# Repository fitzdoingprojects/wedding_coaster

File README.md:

# wedding_coaster
Wedding Coaster

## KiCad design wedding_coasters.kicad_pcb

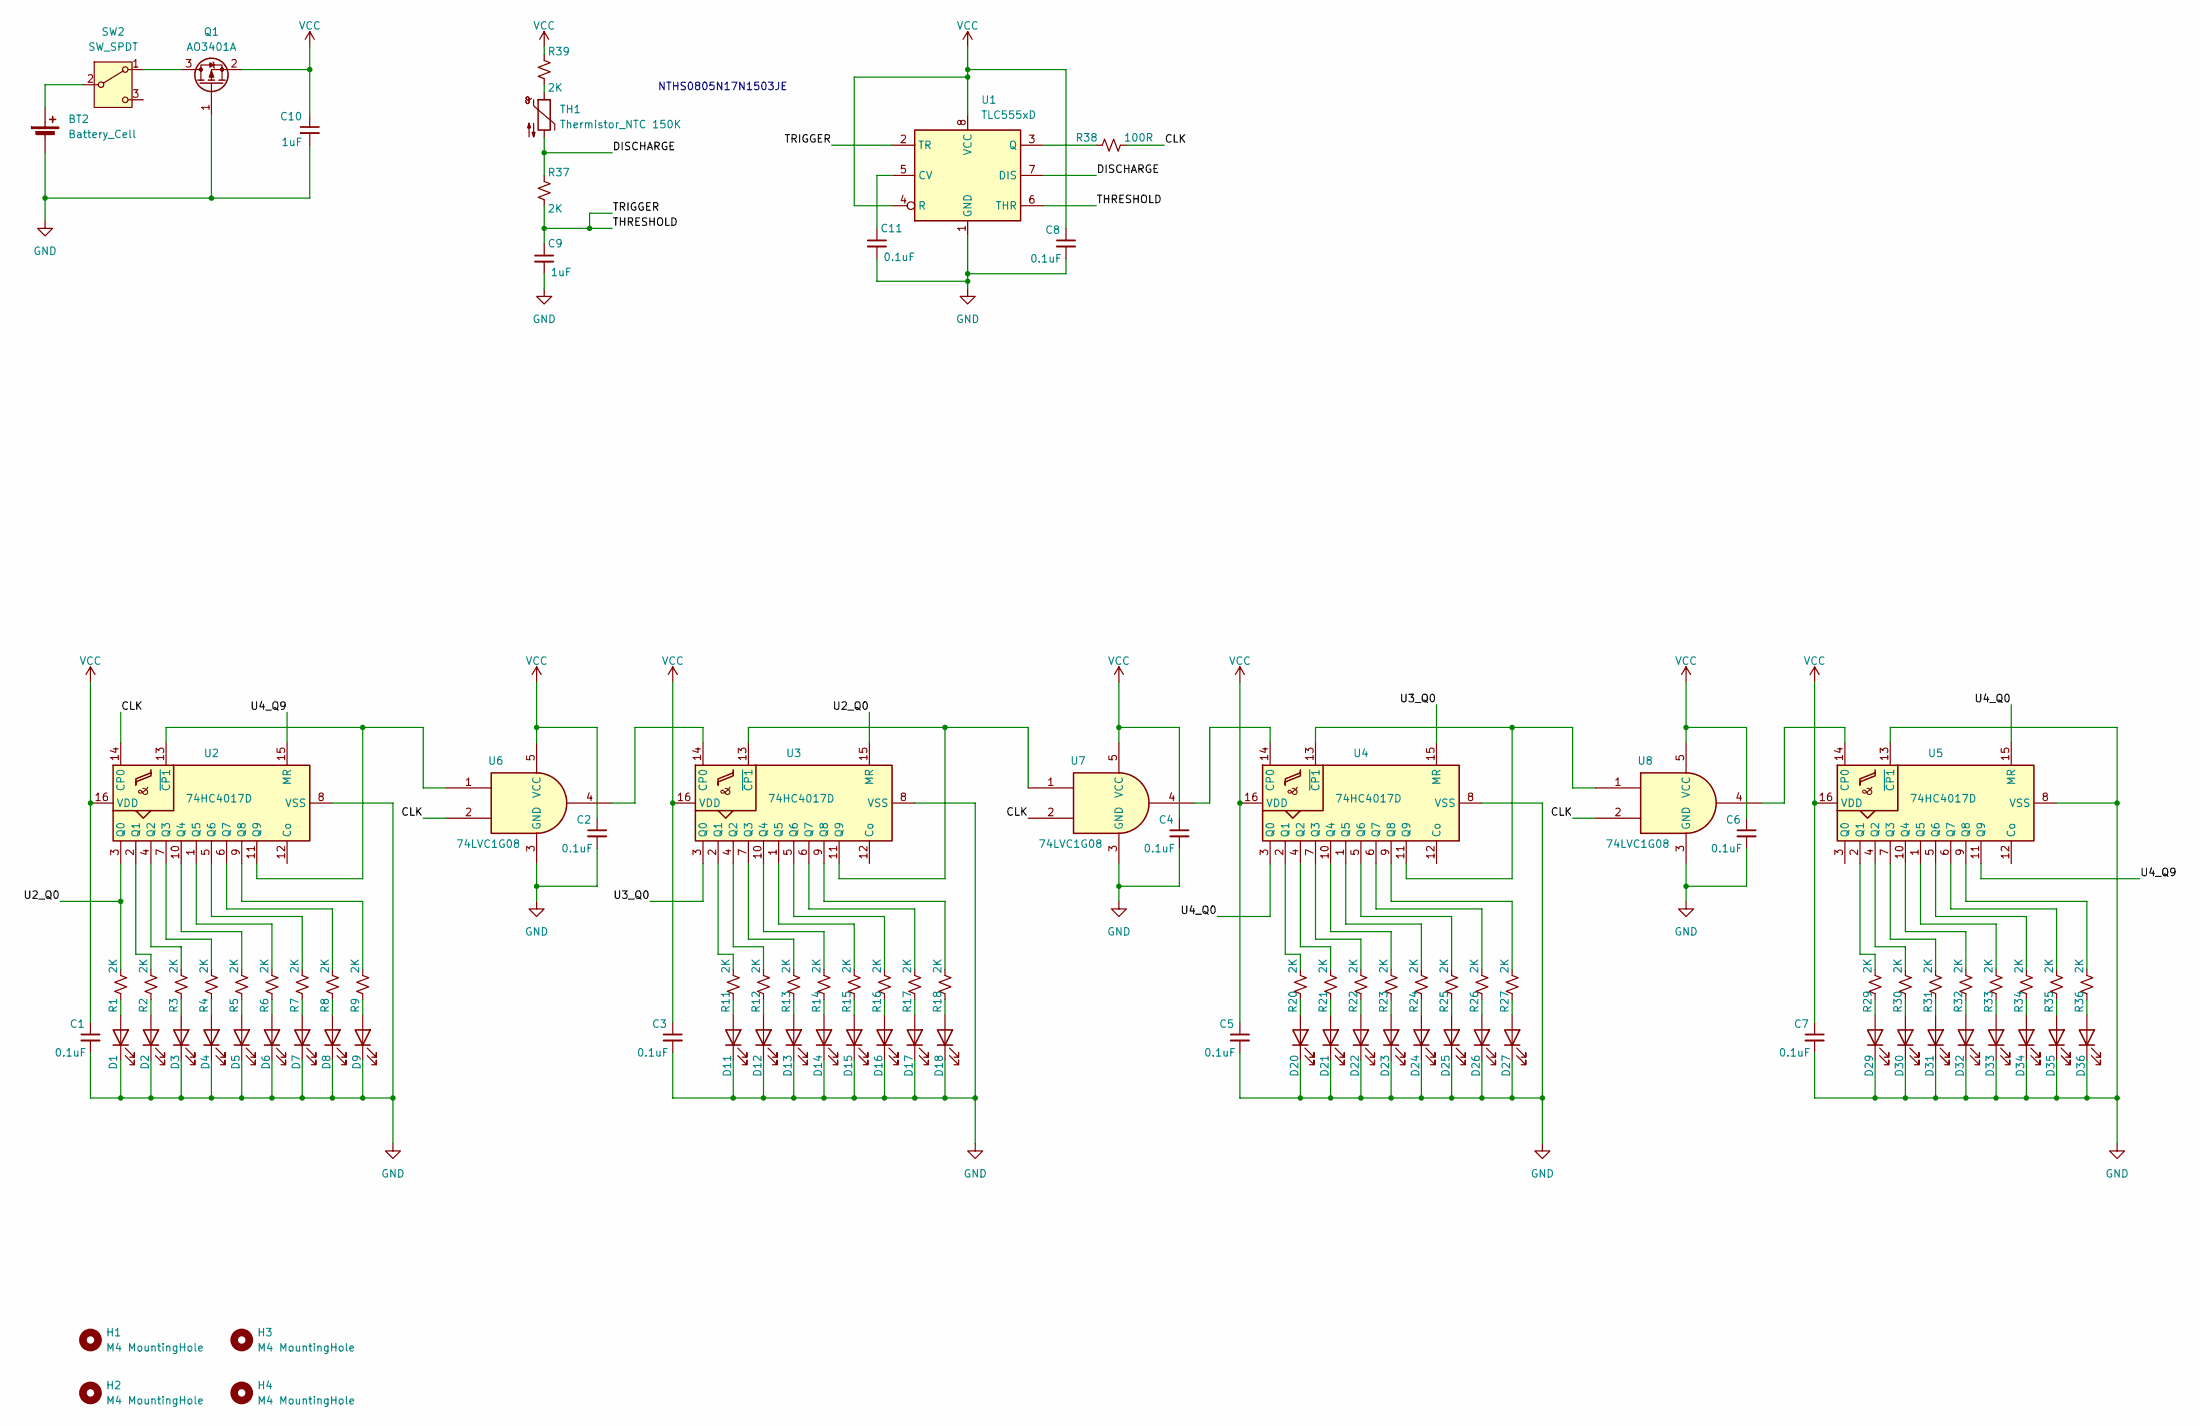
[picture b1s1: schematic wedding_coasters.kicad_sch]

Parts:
BT2: Battery_Cell; BatteryHolder_Keystone_3002_1x2032
C1, C2, C3, C4, C5, C6, C7, C8, C11: 0.1uF; C_0805_2012Metric_Pad1.18x1.45mm_HandSolder
C9, C10: 1uF; C_0805_2012Metric_Pad1.18x1.45mm_HandSolder
D1, D2, D3, D4, D5, D6, D7, D8, D9, D11, D12, D13, D14, D15, D16, D17, D18, D20, D21, D22, D23, D24, D25, D26, D27, D29, D30, D31, D32, D33, D34, D35, D36: LED; D_0805_2012Metric_Pad1.15x1.40mm_HandSolder
H1, H2, H3, H4: M4 MountingHole; MountingHole_4.3mm_M4
Q1: AO3401A; SOT-23
R1, R2, R3, R4, R5, R6, R7, R8, R9, R11, R12, R13, R14, R15, R16, R17, R18, R20, R21, R22, R23, R24, R25, R26, R27, R29, R30, R31, R32, R33, R34, R35, R36, R37, R39: 2K; R_0805_2012Metric_Pad1.20x1.40mm_HandSolder
R38: 100R; R_0805_2012Metric_Pad1.20x1.40mm_HandSolder
SW2: SW_SPDT; SW_SPDT_CK_JS102011SAQN
TH1: Thermistor_NTC 150K; R_0805_2012Metric_Pad1.20x1.40mm_HandSolder
U1: TLC555xD; SOIC-8_3.9x4.9mm_P1.27mm
U2, U3, U4, U5: 74HC4017D; SOIC-16_3.9x9.9mm_P1.27mm
U6, U7, U8: 74LVC1G08; SOT-23-5_HandSoldering

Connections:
/CLK: R38.1, U2.14 (CP0), U6.2, U7.2, U8.2
/DISCHARGE: R37.1, TH1.2, U1.7 (DIS)
/THRESHOLD: C9.1, R37.2, U1.2 (TR), U1.6 (THR)
/U2_Q0: R1.1, U2.3 (Q0), U3.15 (MR)
/U3_Q0: U3.3 (Q0), U4.15 (MR)
/U4_Q0: U4.3 (Q0), U5.15 (MR)
/U4_Q9: U2.15 (MR), U5.11 (Q9)
GND: BT2.2 (-), C1.2, C2.2, C3.2, C4.2, C5.2, C6.2, C7.2, C8.2, C9.2, C10.2, C11.2, D1.1 (K), D2.1 (K), D3.1 (K), D4.1 (K), D5.1 (K), D6.1 (K), D7.1 (K), D8.1 (K), D9.1 (K), D11.1 (K), D12.1 (K), D13.1 (K), D14.1 (K), D15.1 (K), D16.1 (K), D17.1 (K), D18.1 (K), D20.1 (K), D21.1 (K), D22.1 (K), D23.1 (K), D24.1 (K), D25.1 (K), D26.1 (K), D27.1 (K), D29.1 (K), D30.1 (K), D31.1 (K), D32.1 (K), D33.1 (K), D34.1 (K), D35.1 (K), D36.1 (K), Q1.1 (G), U1.1 (GND), U2.8 (VSS), U3.8 (VSS), U4.8 (VSS), U5.8 (VSS), U5.13 (~CP1), U6.3 (GND), U7.3 (GND), U8.3 (GND)
unnamed: BT2.1 (+), SW2.2 (B)
unnamed: D1.2 (A), R1.2
unnamed: D2.2 (A), R2.2
unnamed: D3.2 (A), R3.2
unnamed: D4.2 (A), R4.2
unnamed: D5.2 (A), R5.2
unnamed: D6.2 (A), R6.2
unnamed: D7.2 (A), R7.2
unnamed: D8.2 (A), R8.2
unnamed: D9.2 (A), R9.2
unnamed: D11.2 (A), R11.2
unnamed: D12.2 (A), R12.2
unnamed: D13.2 (A), R13.2
unnamed: D14.2 (A), R14.2
unnamed: D15.2 (A), R15.2
unnamed: D16.2 (A), R16.2
unnamed: D17.2 (A), R17.2
unnamed: D18.2 (A), R18.2
unnamed: D20.2 (A), R20.2
unnamed: D21.2 (A), R21.2
unnamed: D22.2 (A), R22.2
unnamed: D23.2 (A), R23.2
unnamed: D24.2 (A), R24.2
unnamed: D25.2 (A), R25.2
unnamed: D26.2 (A), R26.2
unnamed: D27.2 (A), R27.2
unnamed: D29.2 (A), R29.2
unnamed: D30.2 (A), R30.2
unnamed: D31.2 (A), R31.2
unnamed: D32.2 (A), R32.2
unnamed: D33.2 (A), R33.2
unnamed: D34.2 (A), R34.2
unnamed: D35.2 (A), R35.2
unnamed: D36.2 (A), R36.2
unnamed: Q1.3 (D), SW2.1 (A)
unnamed: R39.2, TH1.1
unnamed: C11.1, U1.5 (CV)
unnamed: R38.2, U1.3 (Q)
unnamed: R2.1, U2.2 (Q1)
unnamed: R3.1, U2.4 (Q2)
unnamed: R4.1, U2.7 (Q3)
unnamed: R5.1, U2.10 (Q4)
unnamed: R6.1, U2.1 (Q5)
unnamed: R7.1, U2.5 (Q6)
unnamed: R8.1, U2.6 (Q7)
unnamed: R9.1, U2.9 (Q8)
unnamed: U2.11 (Q9), U2.13 (~CP1), U6.1
unnamed: U3.14 (CP0), U6.4
unnamed: R11.1, U3.2 (Q1)
unnamed: R12.1, U3.4 (Q2)
unnamed: R13.1, U3.7 (Q3)
unnamed: R14.1, U3.10 (Q4)
unnamed: R15.1, U3.1 (Q5)
unnamed: R16.1, U3.5 (Q6)
unnamed: R17.1, U3.6 (Q7)
unnamed: R18.1, U3.9 (Q8)
unnamed: U3.11 (Q9), U3.13 (~CP1), U7.1
unnamed: U4.14 (CP0), U7.4
unnamed: R20.1, U4.2 (Q1)
unnamed: R21.1, U4.4 (Q2)
unnamed: R22.1, U4.7 (Q3)
unnamed: R23.1, U4.10 (Q4)
unnamed: R24.1, U4.1 (Q5)
unnamed: R25.1, U4.5 (Q6)
unnamed: R26.1, U4.6 (Q7)
unnamed: R27.1, U4.9 (Q8)
unnamed: U4.11 (Q9), U4.13 (~CP1), U8.1
unnamed: U5.14 (CP0), U8.4
unnamed: R29.1, U5.2 (Q1)
unnamed: R30.1, U5.4 (Q2)
unnamed: R31.1, U5.7 (Q3)
unnamed: R32.1, U5.10 (Q4)
unnamed: R33.1, U5.1 (Q5)
unnamed: R34.1, U5.5 (Q6)
unnamed: R35.1, U5.6 (Q7)
unnamed: R36.1, U5.9 (Q8)
VCC: C1.1, C2.1, C3.1, C4.1, C5.1, C6.1, C7.1, C8.1, C10.1, Q1.2 (S), R39.1, U1.4 (R), U1.8 (VCC), U2.16 (VDD), U3.16 (VDD), U4.16 (VDD), U5.16 (VDD), U6.5 (VCC), U7.5 (VCC), U8.5 (VCC)

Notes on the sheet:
NTHS0805N17N1503JE

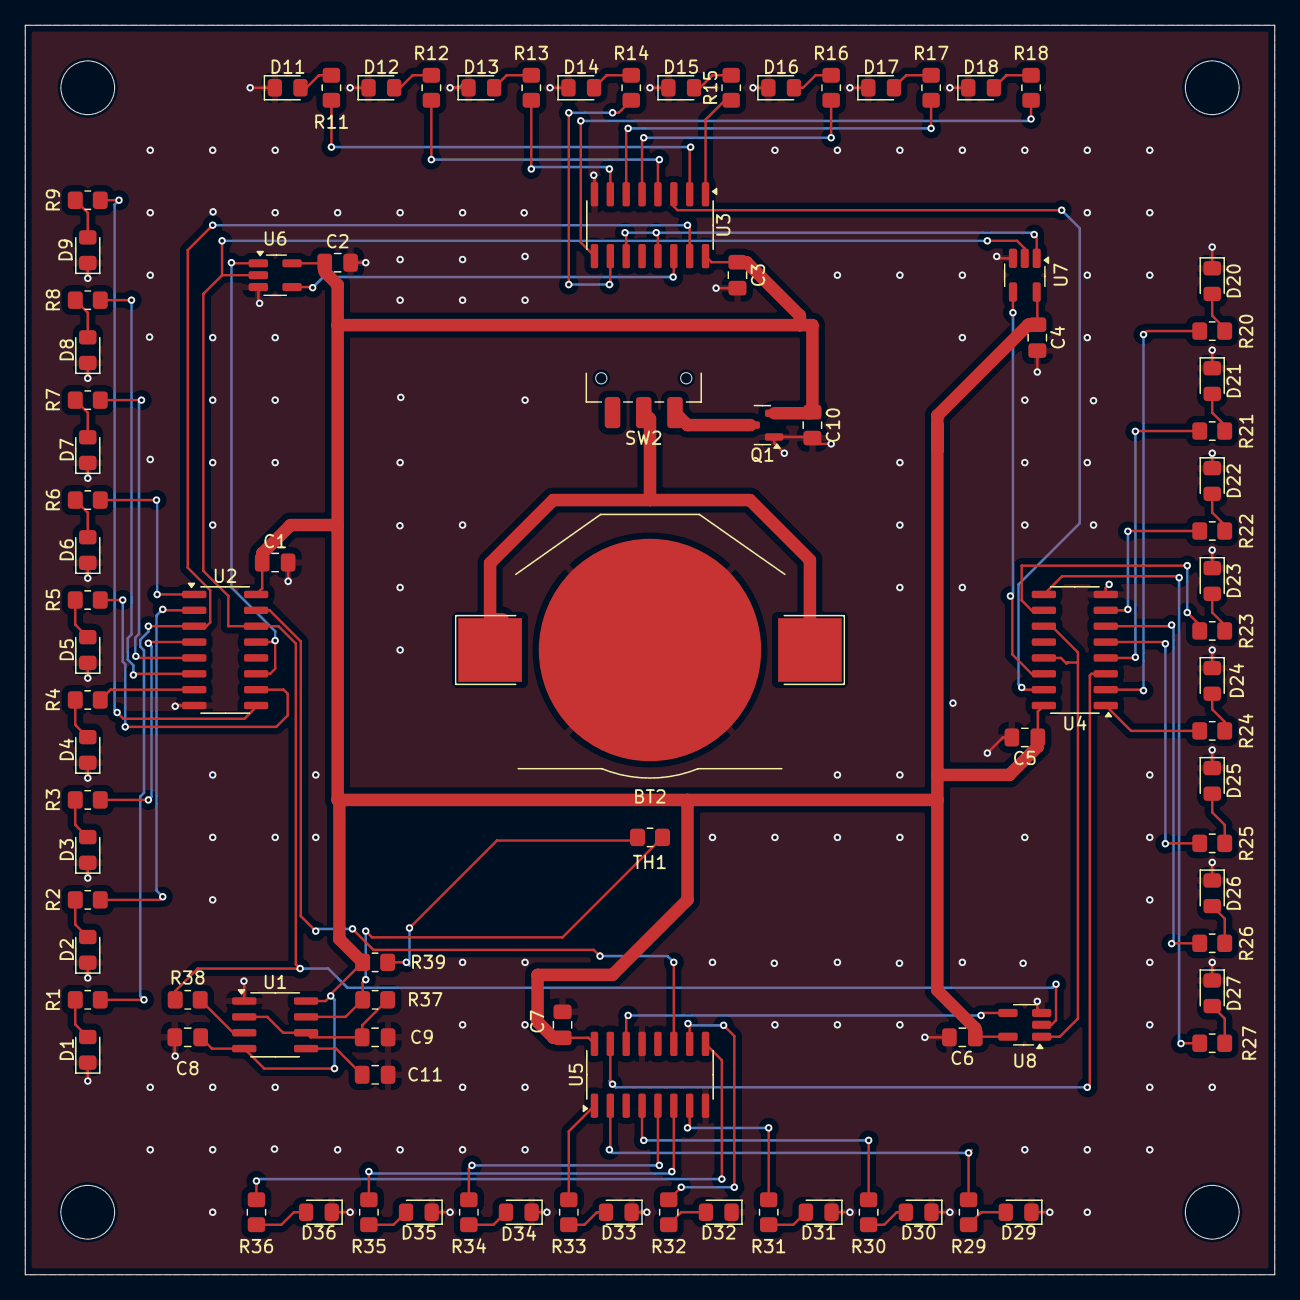
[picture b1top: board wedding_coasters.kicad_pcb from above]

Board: 2 copper layers, 100.0 x 100.0 mm, 96 parts (0 on the bottom side), 85 nets.
